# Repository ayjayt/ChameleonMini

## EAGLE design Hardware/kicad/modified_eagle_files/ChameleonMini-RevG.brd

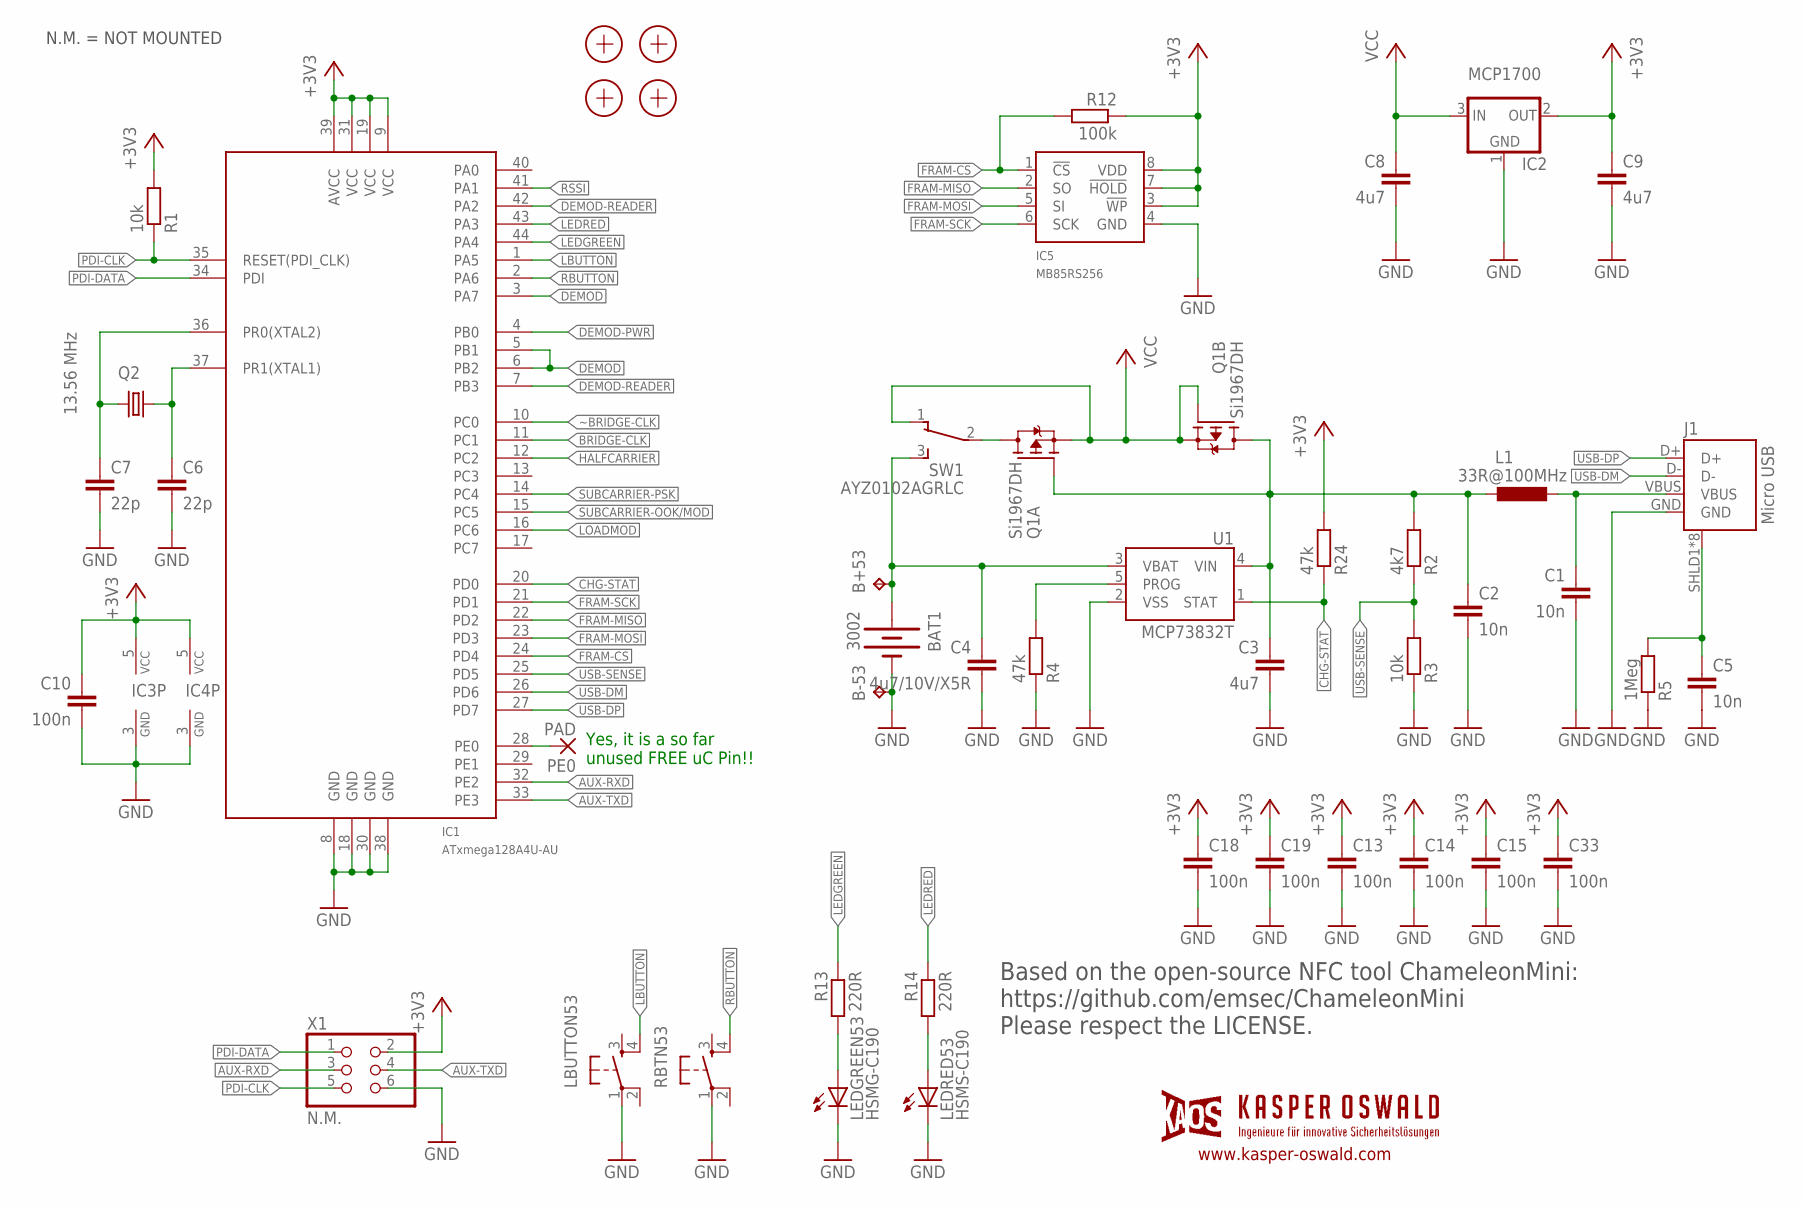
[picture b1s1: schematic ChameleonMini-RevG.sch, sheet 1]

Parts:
B+53: TPTP18SQ; TP18SQ
B-53: TPTP18SQ; TP18SQ
BAT1: 3002; BATTCON_20MM
C1, C2: 10n; C1206K
C3, C8, C9: 4u7; C0603K
C4: 4u7/10V/X5R; C0603K
C5: 10n; C0603K
C6, C7: 22p; C0603K
C10, C13, C14, C15, C18, C19, C33: 100n; C0603K
IC1: ATxmega128A4U-AU; TQFP44
IC2: MCP1700; SOT23
IC3: 7408; SC70-5
IC4: 7486; SC70-5
IC5: MB85RS256; SO-08
J1: Micro USB; USB-MICROB-10118194
L1: 33R@100MHz; L2012C
LBUTTON53: SWITCH_SPST_4_PINSQUARE; TACTILE-SWITCH-SMD
LEDGREEN53: HSMG-C190; CHIPLED-0603
LEDRED53: HSMS-C190; CHIPLED-0603
PE0: PAD; SMD1,27-2,54
Q1: Si1967DH; SOT363
Q2: 13.56 MHz; 5MMX3.2MM
R1, R3: 10k; R0603
R2: 4k7; R0603
R4, R24: 47k; R0603
R5: 1Meg; R0603
R12: 100k; R0603
R13, R14: 220R; R0603
RBTN53: SWITCH_SPST_4_PINSQUARE; TACTILE-SWITCH-SMD
SW1: AYZ0102AGRLC
U1: MCP73832T; SOT23-5
X1: N.M.; PINHD-2X3-2.54-EDGE
X2, X4, X5, X6: PASSER-07; PASSER_07MM

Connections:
+3V3: C9.1, C10.1, C13.1, C14.1, C15.1, C18.1, C19.1, C33.1, IC1.9 (VCC), IC1.19 (VCC), IC1.31 (VCC), IC1.39 (AVCC), IC2.2 (OUT), IC3.5 (VCC), IC4.5 (VCC), IC5.3 (!WP), IC5.7 (!HOLD), IC5.8 (VDD), R1.2, R12.1, R24.2, X1.2; also elsewhere on the board
AUX-RXD: IC1.32 (PE2), X1.3
AUX-TXD: IC1.33 (PE3), X1.4
BRIDGE-CLK: IC1.11 (PC1); also elsewhere on the board
CHG-STAT: IC1.20 (PD0), R24.1, U1.1 (STAT)
DEMOD: IC1.3 (PA7), IC1.5 (PB1), IC1.6 (PB2); also elsewhere on the board
DEMOD-PWR: IC1.4 (PB0); also elsewhere on the board
DEMOD-READER: IC1.7 (PB3), IC1.42 (PA2); also elsewhere on the board
FRAM-CS: IC1.24 (PD4), IC5.1 (!CS), R12.2
FRAM-MISO: IC1.22 (PD2), IC5.2 (SO)
FRAM-MOSI: IC1.23 (PD3), IC5.5 (SI)
FRAM-SCK: IC1.21 (PD1), IC5.6 (SCK)
GND: B-53.TP, BAT1.-, C1.2, C2.2, C3.2, C4.2, C5.2, C6.2, C7.2, C8.2, C9.2, C10.2, C13.2, C14.2, C15.2, C18.2, C19.2, C33.2, IC1.8 (GND), IC1.18 (GND), IC1.30 (GND), IC1.38 (GND), IC2.1 (GND), IC3.3 (GND), IC4.3 (GND), IC5.4 (GND), J1.GND, LBUTTON53.1, LEDGREEN53.C, LEDRED53.C, R3.1, R4.1, R5.1, RBTN53.1, U1.2 (VSS), X1.6; also elsewhere on the board
HALFCARRIER: IC1.12 (PC2); also elsewhere on the board
LBUTTON: IC1.1 (PA5), LBUTTON53.4
LEDGREEN: IC1.44 (PA4), R13.1
LEDRED: IC1.43 (PA3), R14.1
LOADMOD: IC1.16 (PC6); also elsewhere on the board
unnamed: C7.1, IC1.36 (PR0(XTAL2)), Q2.3 (2)
unnamed: C1.1, J1.VBUS, L1.1
unnamed: C6.1, IC1.37 (PR1(XTAL1)), Q2.1
unnamed: LEDGREEN53.A, R13.2
unnamed: LEDRED53.A, R14.2
unnamed: Q1.6 (D), SW1.2
unnamed: C2.1, C3.1, L1.2, Q1.2 (G), Q1.3 (D), R2.2, U1.4 (VIN)
unnamed: IC1.28 (PE0), PE0.1
unnamed: R4.2, U1.5 (PROG)
unnamed: B+53.TP, BAT1.+2 (+), C4.1, SW1.3 (S), U1.3 (VBAT)
unnamed: C5.1, J1.SHLD1 (SHIELD), J1.SHLD2 (SHIELD), J1.SHLD3 (SHIELD), J1.SHLD4 (SHIELD), J1.SHLD5 (SHIELD), J1.SHLD6 (SHIELD), J1.SHLD7 (SHIELD), J1.SHLD8 (SHIELD), R5.2
PDI-CLK: IC1.35 (RESET(PDI_CLK)), R1.1, X1.5
PDI-DATA: IC1.34 (PDI), X1.1
RBUTTON: IC1.2 (PA6), RBTN53.4
RSSI: IC1.41 (PA1); also elsewhere on the board
SUBCARRIER-OOK/MOD: IC1.15 (PC5); also elsewhere on the board
SUBCARRIER-PSK: IC1.14 (PC4); also elsewhere on the board
USB-DM: IC1.26 (PD6), J1.D-
USB-DP: IC1.27 (PD7), J1.D+
USB-SENSE: IC1.25 (PD5), R2.1, R3.2
VCC: C8.1, IC2.3 (IN), Q1.1 (S), Q1.4 (S), Q1.5 (G), SW1.1 (O)
~BRIDGE-CLK: IC1.10 (PC0); also elsewhere on the board

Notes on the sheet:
Based on the open-source NFC tool ChameleonMini: https://github.com/emsec/ChameleonMini Please respect the LICENSE.
N.M. = NOT MOUNTED
Yes, it is a so far unused FREE uC Pin!!
www.kasper-oswald.com

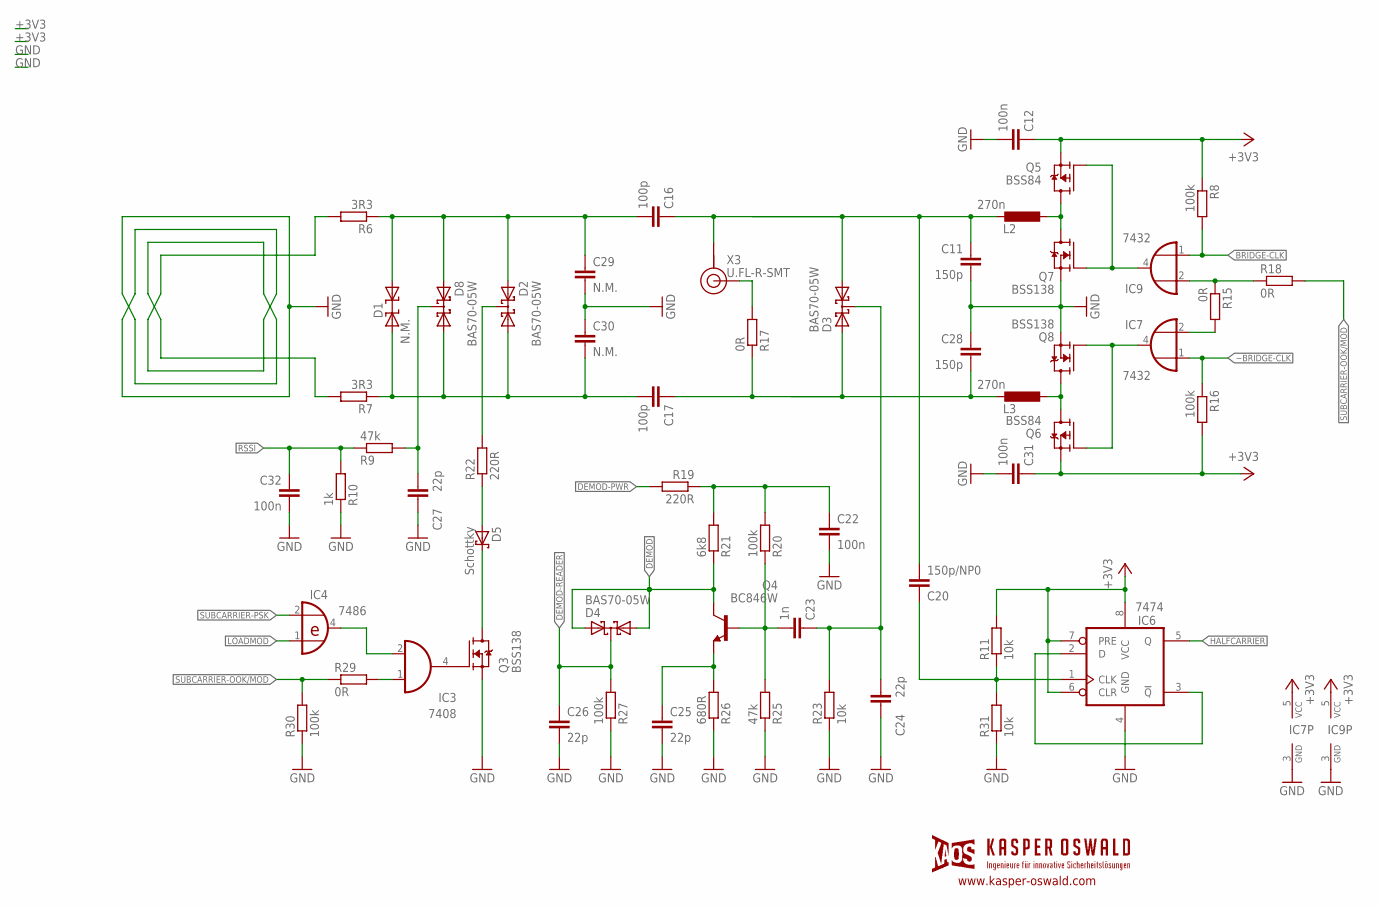
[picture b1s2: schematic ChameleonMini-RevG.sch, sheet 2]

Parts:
C11, C28: 150p; C0603K
C12, C22, C31, C32: 100n; C0603K
C16, C17: 100p; C0603K
C20: 150p/NP0; C0603K
C23: 1n; C0603K
C24, C25, C26, C27: 22p; C0603K
C29, C30: N.M.; C0603K
D1: N.M.; DO214AC
D2, D3, D4, D8: BAS70-05W; SOT323
D5: Schottky; SOD323(F)
IC3: 7408; SC70-5
IC4: 7486; SC70-5
IC6: 7474; VSSOP8
IC7, IC9: 7432; SC70-5
L2, L3: 270n; L2012C
Q3, Q7, Q8: BSS138; SOT323
Q4: BC846W; SOT323
Q5, Q6: BSS84; SOT323
R6, R7: 3R3; R0603
R8, R16, R20, R27, R30: 100k; R0603
R9, R25: 47k; R0603
R10: 1k; R0603
R11, R23, R31: 10k; R0603
R15, R17, R18, R29: 0R; R0603
R19, R22: 220R; R0603
R21: 6k8; R0603
R26: 680R; R0603
X3: U.FL-R-SMT

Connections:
+3V3: C12.1, C31.1, IC6.6 (CLR), IC6.7 (PRE), IC6.8 (VCC), IC7.5 (VCC), IC9.5 (VCC), Q5.2 (S), Q6.2 (S), R8.1, R11.2, R16.2; also elsewhere on the board
ANTENNA-A: C11.1, C16.1, C20.2, D3.2 (A2), L2.2, X3.GND1 (GND)
ANTENNA-B: C17.1, C28.2, D3.1 (A1), L3.2, R17.1
BRIDGE-1: IC9.4 (O), Q5.1 (G), Q7.1 (G)
BRIDGE-2: IC7.4 (O), Q6.1 (G), Q8.1 (G)
BRIDGE-CLK: IC9.1 (I0), R8.2; also elsewhere on the board
DEMOD: D4.1 (A1), D4.2 (A2), Q4.3 (C), R21.1; also elsewhere on the board
DEMOD-PWR: R19.2; also elsewhere on the board
DEMOD-READER: C26.1, D4.3 (K), R27.2; also elsewhere on the board
GND: C11.2, C12.2, C22.2, C24.2, C25.2, C26.2, C27.2, C28.1, C29.2, C30.1, C31.2, C32.2, IC6.4 (GND), IC7.3 (GND), IC9.3 (GND), Q3.2 (S), Q7.2 (S), Q8.2 (S), R6.2, R7.2, R10.1, R23.1, R25.1, R26.1, R27.1, R30.1, R31.1; also elsewhere on the board
HALFCARRIER: IC6.5 (Q); also elsewhere on the board
LOADMOD: IC4.1 (I0); also elsewhere on the board
MOD-DEMOD: D2.3 (K), R22.2
MOD-DEMOD1: C23.1, C24.1, D3.3 (K), R23.2
unnamed: C25.1, Q4.2 (E), R26.2
unnamed: IC7.2 (I1), R15.2
unnamed: D5.1 (K), Q3.3 (D)
unnamed: IC6.2 (D), IC6.3 (!Q)
unnamed: C16.2, C29.1, D1.2, D2.1 (A1), D8.1 (A1), R6.1
unnamed: L2.1, Q5.3 (D), Q7.3 (D)
unnamed: IC3.2 (I1), IC4.4 (O)
unnamed: D5.2 (A), R22.1
unnamed: IC3.4 (O), Q3.1 (G)
unnamed: R17.2, X3.SIG
unnamed: L3.1, Q6.3 (D), Q8.3 (D)
unnamed: C17.2, C30.2, D1.1, D2.2 (A2), D8.2 (A2), R7.1
unnamed: C27.1, D8.3 (K), R9.2
unnamed: IC9.2 (I1), R15.1, R18.1
unnamed: C23.2, Q4.1 (B), R20.1, R25.2
unnamed: C20.1, IC6.1 (CLK), R11.1, R31.2
unnamed: IC3.1 (I0), R29.2
unnamed: C22.1, R19.1, R20.2, R21.2
RSSI: C32.1, R9.1, R10.2; also elsewhere on the board
SUBCARRIER-OOK/MOD: R18.2, R29.1, R30.2; also elsewhere on the board
SUBCARRIER-PSK: IC4.2 (I1); also elsewhere on the board
~BRIDGE-CLK: IC7.1 (I0), R16.1; also elsewhere on the board

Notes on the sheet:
www.kasper-oswald.com

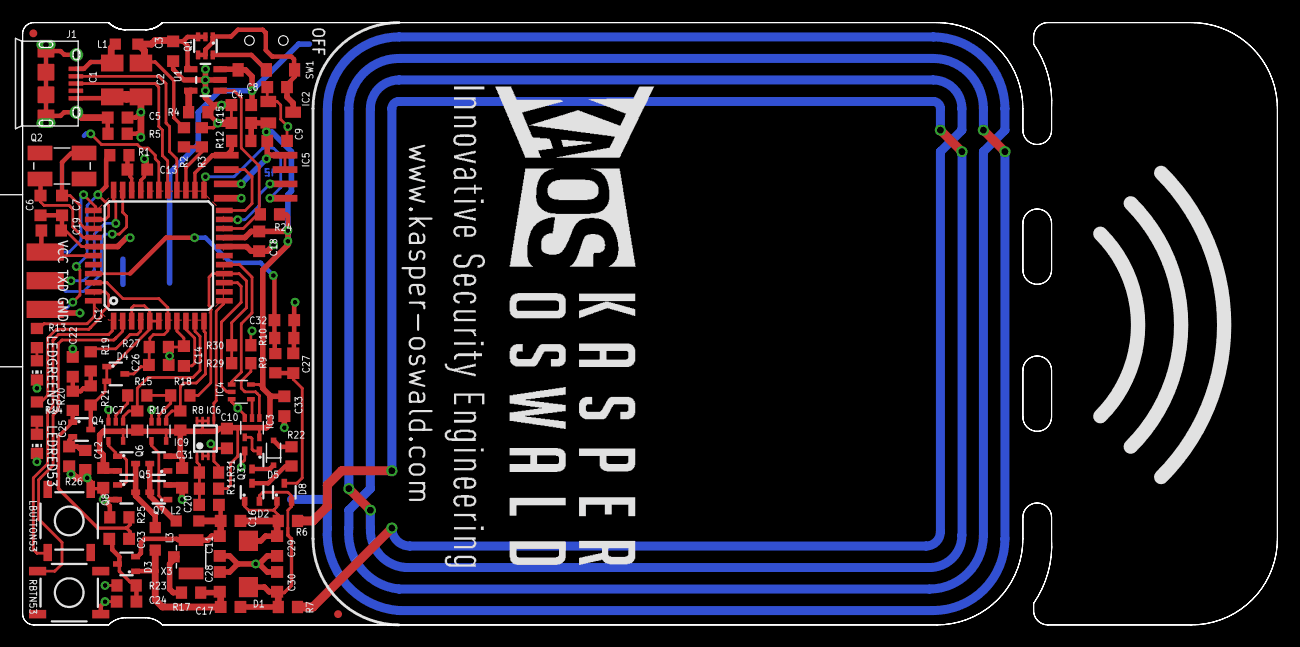
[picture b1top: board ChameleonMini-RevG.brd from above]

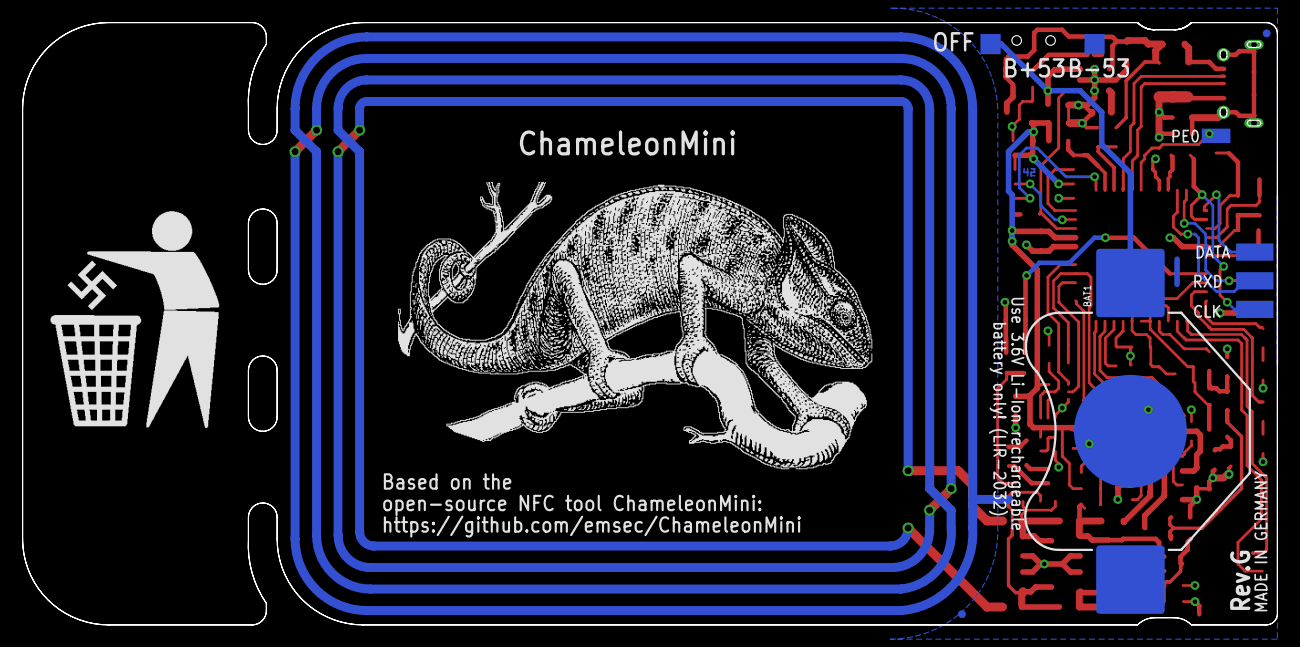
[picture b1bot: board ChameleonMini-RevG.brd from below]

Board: 2 copper layers, 111.1 x 53.3 mm, 104 parts (6 on the bottom side), 64 nets.

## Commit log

2017-09-20 Added two non-firmware things:
    A folder generated during conversion to kicad- nothing useful
    Fixed a 1k to be the proper size
2017-09-21 UART WORKS! Added some functions Some notes too, (how to turn off USB)
2017-10-06 tons of uart working
2017-10-14 UART now works as a library to trade commands- no XMODEM yet
2017-10-14 added a .gitignore for vim
2017-11-07 Modified so UART works with XMODEM
    XMODEM doesn't use \r to indicate commands, so I added 0x01 and 0x04 to mark that buffer should
    be processed

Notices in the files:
parts and their libraries:
SparkFun-Electromechanical: Licensing: Creative Commons ShareAlike 4.0 International - https://creativecommons.org/licenses/by-sa/4.0
